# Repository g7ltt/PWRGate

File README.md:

# PWRGate
12V standby power from a battery when using a 12V PSU. Designed for ham radio appications

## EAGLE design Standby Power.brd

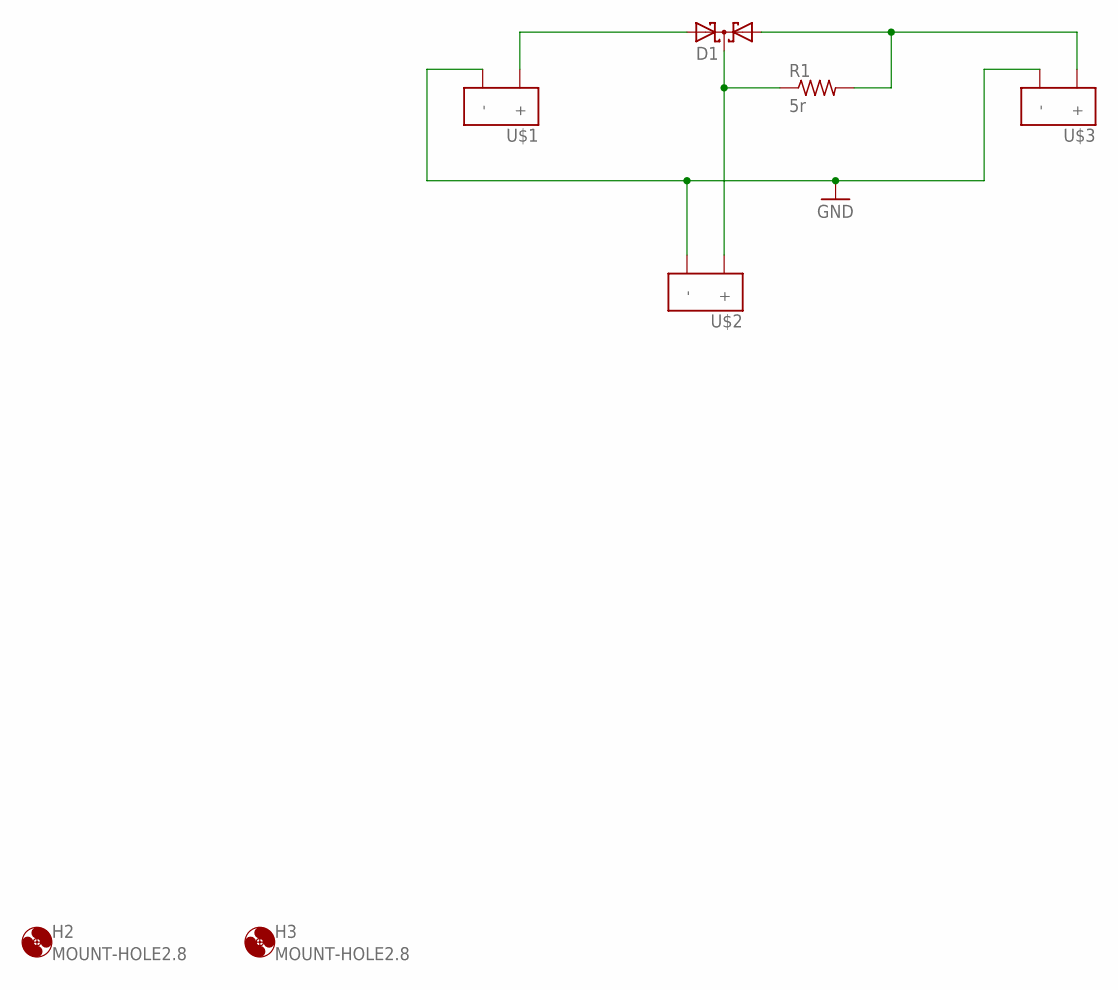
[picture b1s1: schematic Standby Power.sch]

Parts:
D1: DIODE_2SCHOTTKY-SOT82H; SOT82L
H2, H3: MOUNT-HOLE2.8; 2,8
R1: 5r; V235/17
U$1, U$2, U$3: POWERPOLE-HORZ-NARROW-CONTACT; HORZ-NARROW-CONTACT

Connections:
GND: U$1.-, U$2.-, U$3.-
unnamed: D1.A2, U$1.+
unnamed: D1.A1, R1.2, U$3.+
unnamed: D1.C, R1.1, U$2.+

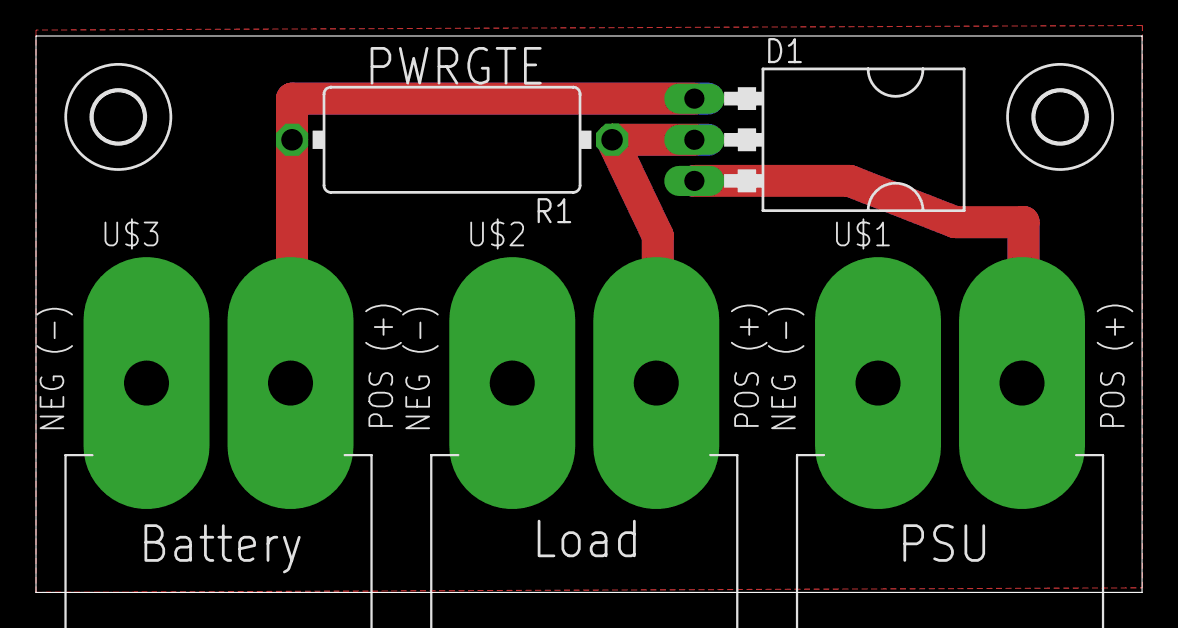
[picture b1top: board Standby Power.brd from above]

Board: 2 copper layers, 61.4 x 30.9 mm, 7 parts (0 on the bottom side), 4 nets.
